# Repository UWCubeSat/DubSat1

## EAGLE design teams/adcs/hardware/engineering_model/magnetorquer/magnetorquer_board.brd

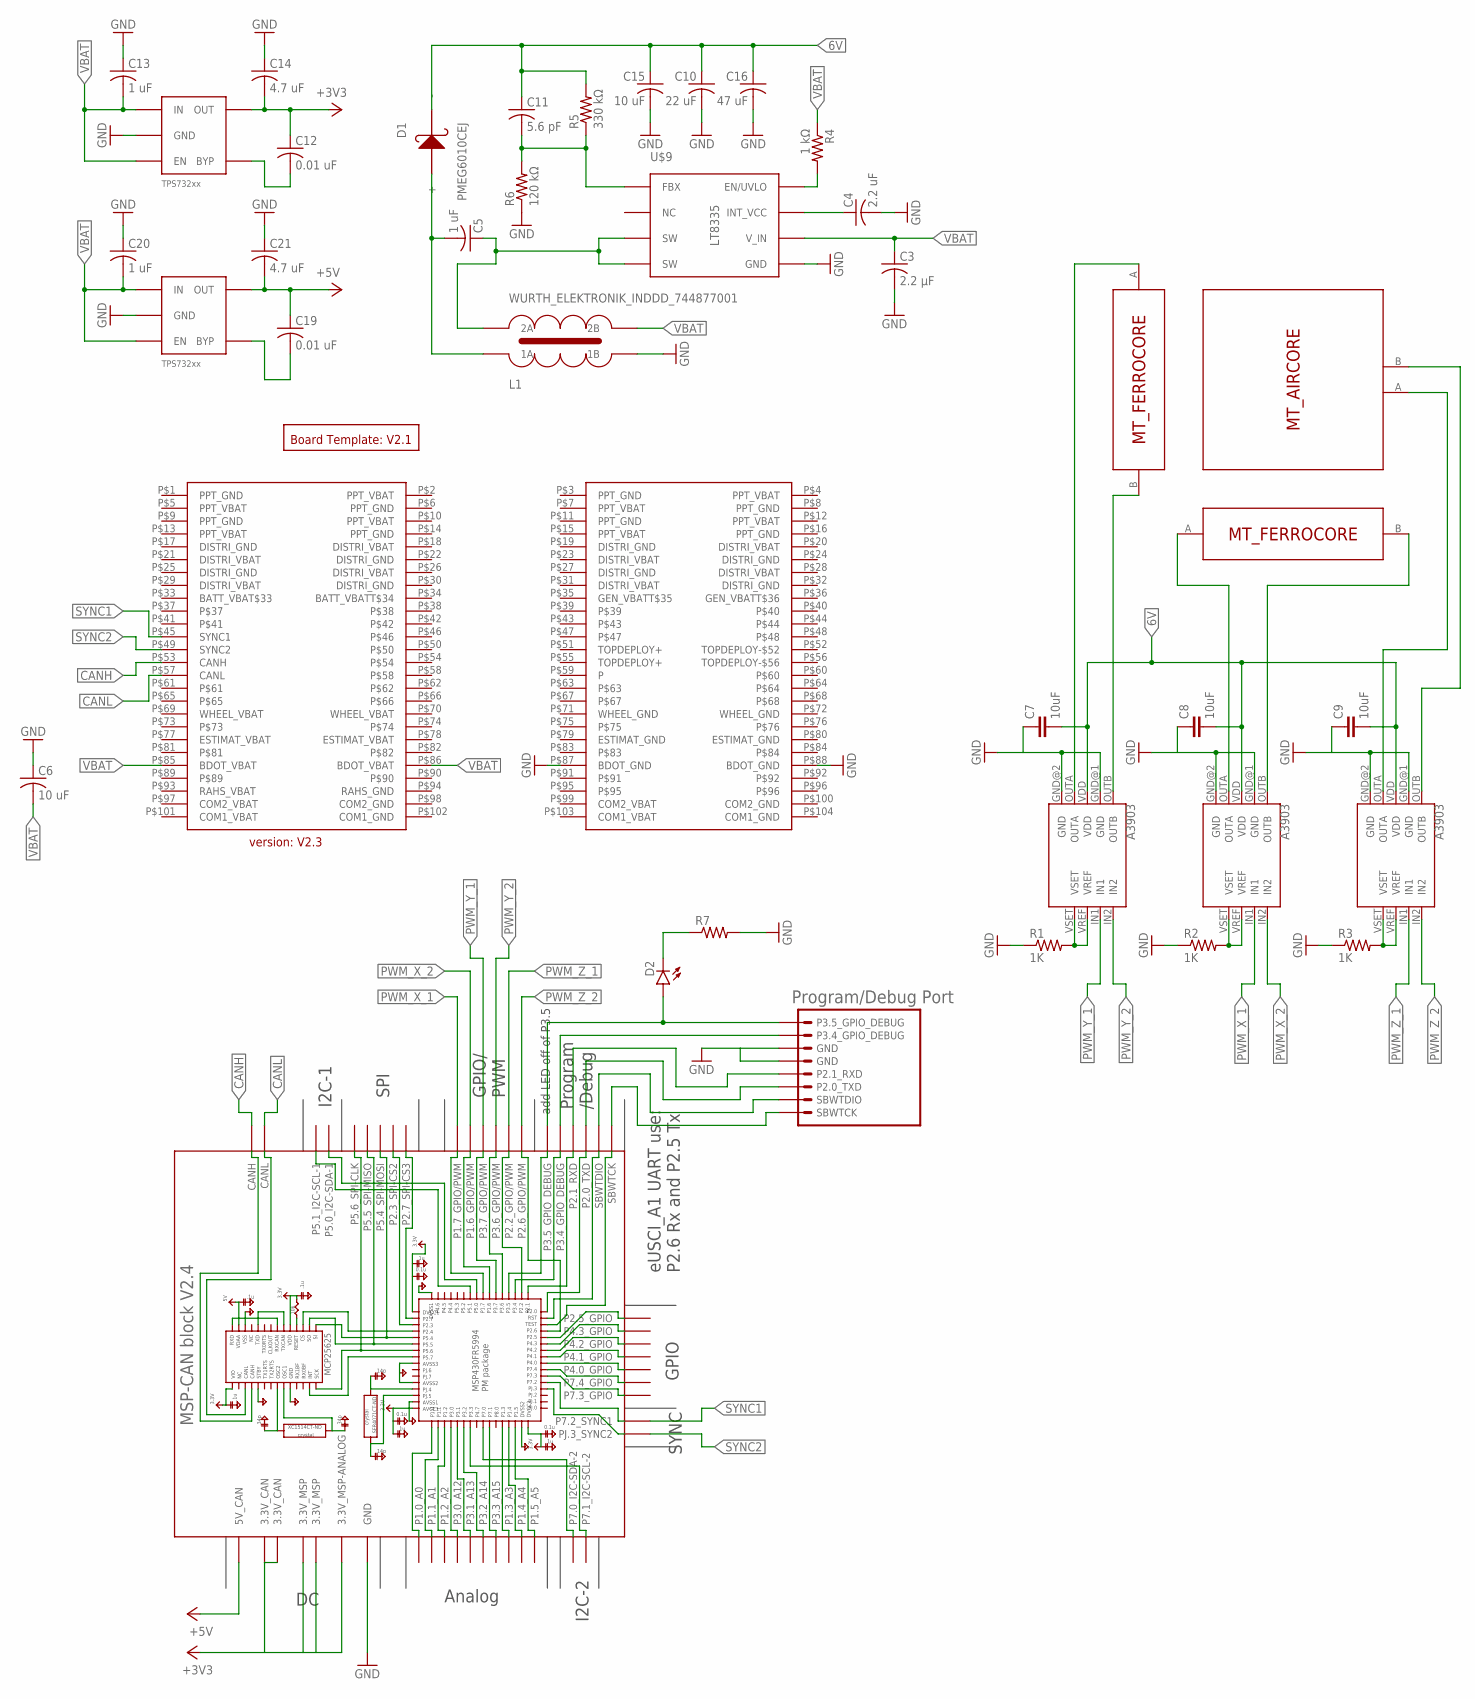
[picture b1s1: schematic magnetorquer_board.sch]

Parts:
C3: 2.2 μF; C0805
C4: 2.2 uF; C0805
C5, C13, C20: 1 uF; C0805
C6, C15: 10 uF; C0805
C7, C8, C9: 10uF; C0805
C10: 22 uF; C1206
C11: 5.6 pF; C0805
C12, C19: 0.01 uF; C0805
C14, C21: 4.7 uF; C0805
C16: 47 uF; C1206
D1: PMEG6010CEJ; SC-90
D2: LED; LED-1206
L1: WURTH_ELEKTRONIK_INDDD_744877001
LDO_3V1, LDO_5V1: TPS732XX; SOT-23-5
R1, R2, R3: 1K; R0603
R4: 1 kΩ; 0805
R5: 330 kΩ; 0805
R6: 120 kΩ; 0805
R7: RESISTOR0805; 0805
U1, U2, U3: A3903; DFN-8EE
U$1: PC104_CONNECTOR
U$2: BOARD_TEMPLATE1; BOARD_TEMPLATE
U$3: MT_AIRCORE
U$4, U$5: MT_FERROCORE
U$7: MSP-CAN_BLOCK
U$8: PROGRAM/DEBUG_PORT; 1X08_CONNECTOR
U$9: LT8335; DDB

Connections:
6V: C7.2, C8.2, C9.2, C10.1, C11.1, C15.1, C16.1, D1.P$2 (-), R5.2, U1.VDD, U2.VDD, U3.VDD
+3V3: C12.1, C14.2, LDO_3V1.P$5 (OUT), U$7.3.3V@CAN1 (3.3V_CAN), U$7.3.3V@CAN2 (3.3V_CAN), U$7.3.3V@MSP1 (3.3V_MSP), U$7.3.3V@MSP2 (3.3V_MSP), U$7.3.3V_ANALOG@MSP2 (3.3V_MSP-ANALOG)
+5V: C19.1, C21.2, LDO_5V1.P$5 (OUT), U$7.5V (5V_CAN)
CANH: U$1.P$53 (CANH), U$7.CANH
CANL: U$1.P$57 (CANL), U$7.CANL
EN_UVLO1: R4.2, U$9.P$8 (EN/UVLO)
FBX: C11.2, R5.1, R6.2, U$9.P$1 (FBX)
GND: C3.2, C4.2, C6.1, C7.1, C8.1, C9.1, C10.2, C13.1, C14.1, C15.2, C16.2, C20.1, C21.1, L1.P$2 (1B), LDO_3V1.P$2 (GND), LDO_5V1.P$2 (GND), R1.1, R2.1, R3.1, R6.1, R7.2, U1.GND@1 (GND), U1.GND@2 (GND), U2.GND@1 (GND), U2.GND@2 (GND), U3.GND@1 (GND), U3.GND@2 (GND), U$1.P$87 (BDOT_GND), U$1.P$88 (BDOT_GND), U$7.GND@1 (GND), U$7.GND@2 (GND), U$7.GND@3 (GND), U$7.GND@4 (GND), U$7.GND@5 (GND), U$7.GND@7 (GND), U$7.GND@8 (GND), U$7.GND@9 (GND), U$7.GND@10 (GND), U$7.GND@11 (GND), U$7.GND@12 (GND), U$7.GND@13 (GND), U$7.GND@14 (GND), U$7.GND@15 (GND), U$7.GND@16 (GND), U$7.GND@17 (GND), U$7.GND@26 (GND), U$8.5 (GND), U$8.6 (GND), U$9.GND, U$9.P$5 (GND)
INT_VCC: C4.1, U$9.P$7 (INT_VCC)
unnamed: R1.2, U1.VREF, U1.VSET
unnamed: R2.2, U2.VREF, U2.VSET
unnamed: D2.C, R7.1
unnamed: C12.2, LDO_3V1.P$4 (BYP)
unnamed: R3.2, U3.VREF, U3.VSET
unnamed: C19.2, LDO_5V1.P$4 (BYP)
unnamed: U1.OUTB, U$4.B
unnamed: U1.OUTA, U$4.A
unnamed: U2.OUTA, U$5.A
unnamed: U2.OUTB, U$5.B
unnamed: U3.OUTB, U$3.B
unnamed: U3.OUTA, U$3.A
unnamed: U$7.SBWTCK, U$8.SBWTCK
unnamed: U$7.SBWTDIO, U$8.2 (SBWTDIO)
unnamed: U$7.P2.0_TXD, U$8.3 (P2.0_TXD)
unnamed: U$7.P2.1_RXD, U$8.4 (P2.1_RXD)
unnamed: U$7.P3.4_GPIO_DEBUG, U$8.7 (P3.4_GPIO_DEBUG)
unnamed: D2.A, U$7.P3.5_GPIO_DEBUG, U$8.8 (P3.5_GPIO_DEBUG)
PWM_X_1: U2.IN1, U$7.P1.7_GPIO/PWM
PWM_X_2: U2.IN2, U$7.P1.6_GPIO/PWM
PWM_Y_1: U1.IN1, U$7.P3.7_GPIO/PWM
PWM_Y_2: U1.IN2, U$7.P3.6_GPIO/PWM
PWM_Z_1: U3.IN1, U$7.P2.2_GPIO/PWM
PWM_Z_2: U3.IN2, U$7.P2.6_GPIO/PWM
SW: C5.1, L1.P$3 (2A), U$9.P$3 (SW), U$9.P$4 (SW)
SYNC1: U$1.P$45 (SYNC1), U$7.P7.2_SYNC1
SYNC2: U$1.P$49 (SYNC2), U$7.PJ.3_SYNC2
VBAT: C3.1, C6.2, C13.2, C20.2, L1.P$4 (2B), LDO_3V1.P$1 (IN), LDO_3V1.P$3 (EN), LDO_5V1.P$1 (IN), LDO_5V1.P$3 (EN), R4.1, U$1.P$85 (BDOT_VBAT), U$1.P$86 (BDOT_VBAT), U$9.P$6 (V_IN)
VD: C5.2, D1.P$1 (+), L1.P$1 (1A)

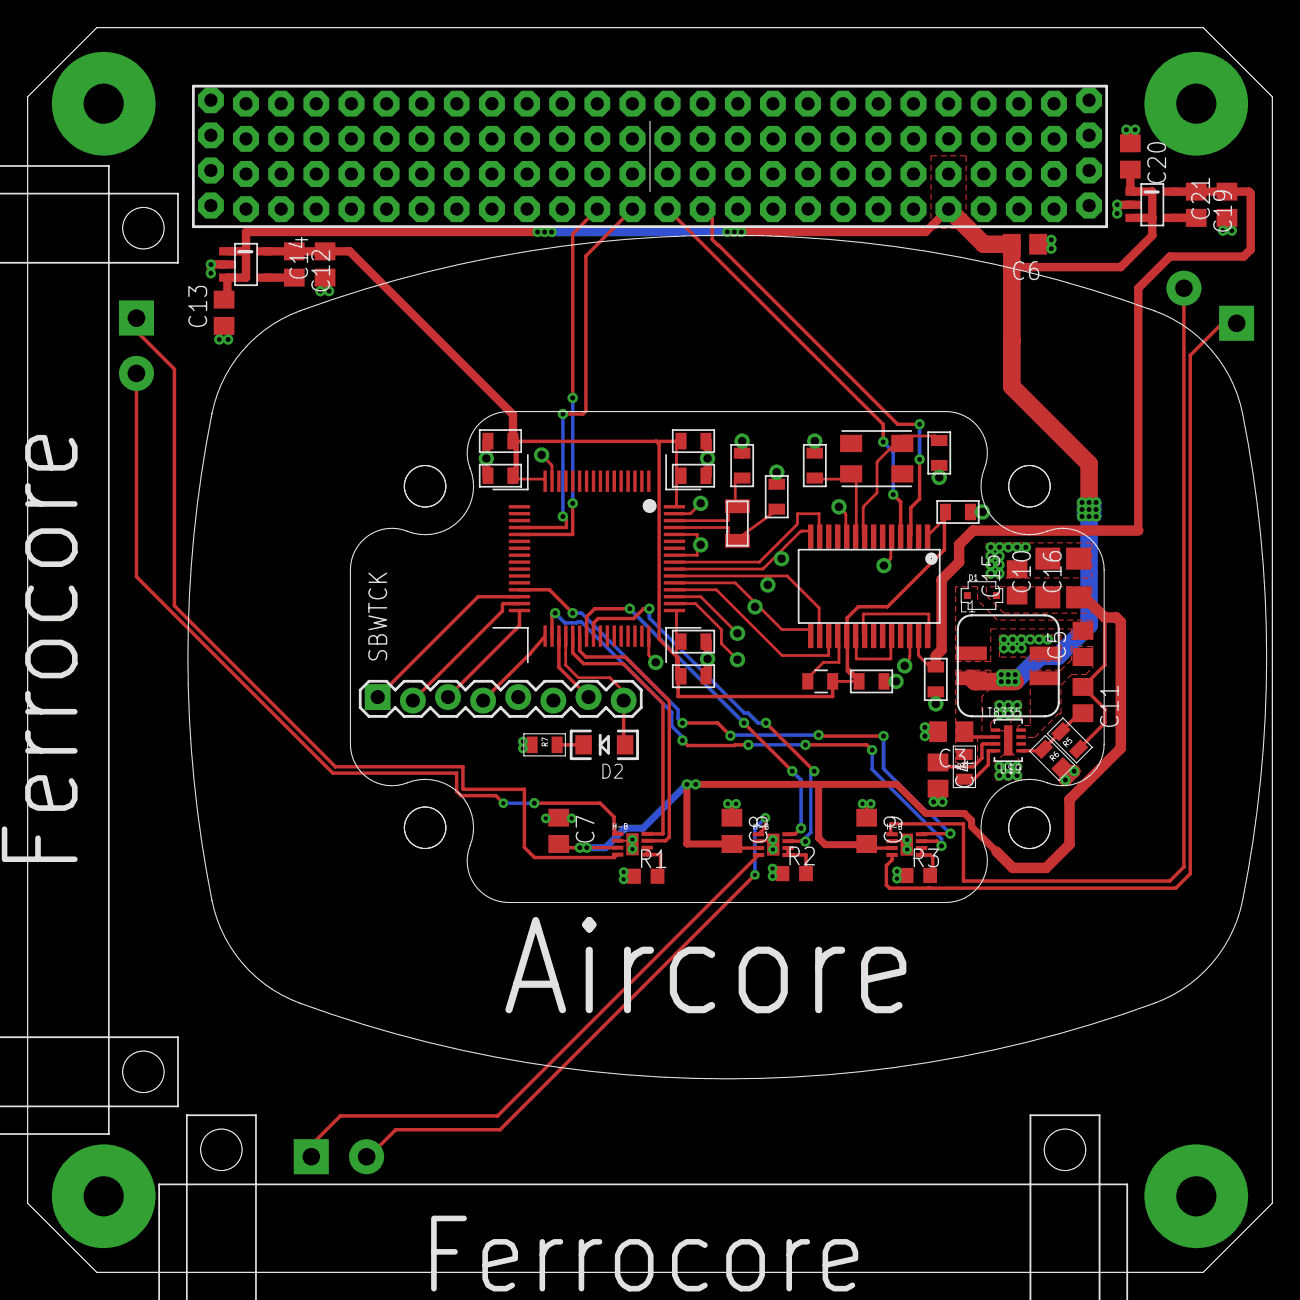
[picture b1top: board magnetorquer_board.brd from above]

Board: 2 copper layers, 90.0 x 90.0 mm, 40 parts (0 on the bottom side), 38 nets.

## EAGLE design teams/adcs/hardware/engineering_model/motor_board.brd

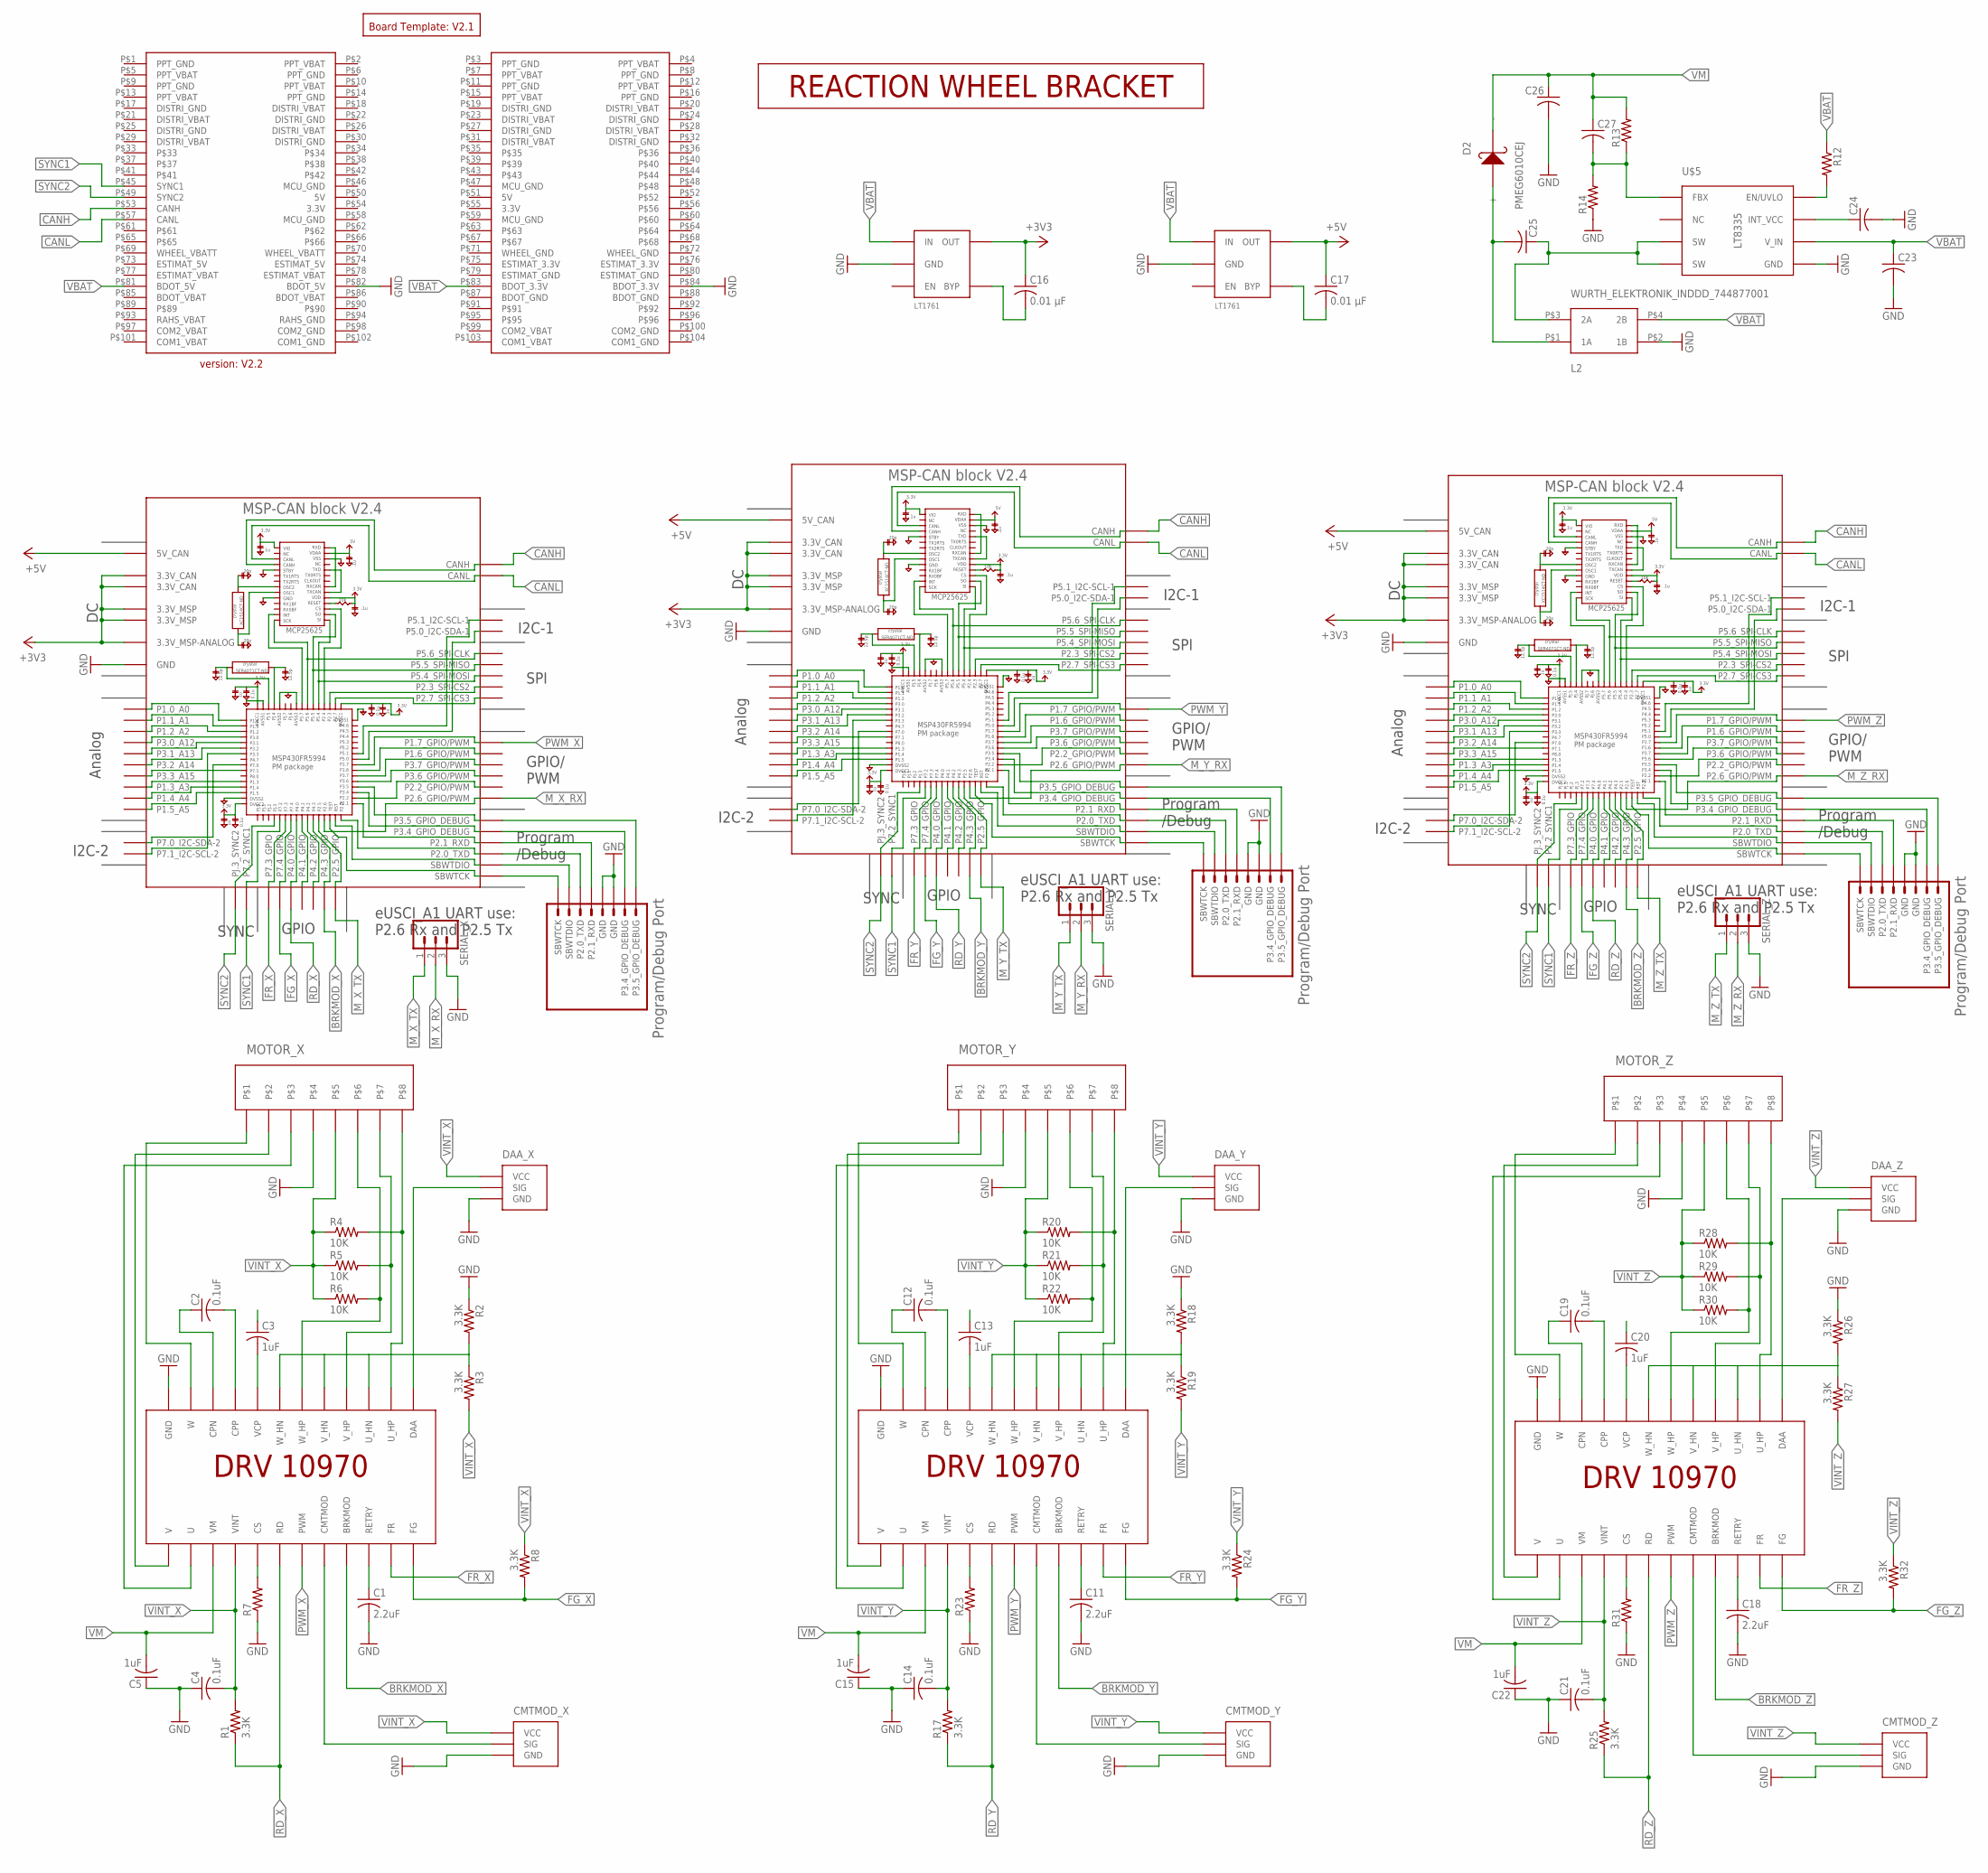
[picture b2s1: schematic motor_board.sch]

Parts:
C1, C11, C18: 2.2uF; C1206
C2, C4, C12, C14, C19, C21: 0.1uF; C0805
C3, C5, C13, C15, C20, C22: 1uF; C1206
C16, C17: 0.01 μF; C0805
C23, C24, C25, C26, C27: C-USC0805; C0805
CMTMOD_X: 0_OHM_JUMPER
CMTMOD_Y: 0_OHM_JUMPER
CMTMOD_Z: 0_OHM_JUMPER
D2: PMEG6010CEJ; SC-90
DAA_X: 0_OHM_JUMPER
DAA_Y: 0_OHM_JUMPER
DAA_Z: 0_OHM_JUMPER
L2: WURTH_ELEKTRONIK_INDDD_744877001
LDO_3V3, LDO_5V: LINEAR_LDO_LT1761-X; SOT-23-5
MOTOR_X: PICOLOCK_8
MOTOR_Y: PICOLOCK_8
MOTOR_Z: PICOLOCK_8
R1, R2, R3, R8, R17, R18, R19, R24, R25, R26, R27, R32: 3.3K; R0805
R4, R5, R6, R20, R21, R22, R28, R29, R30: 10K; R0805
R7, R12, R13, R14, R23, R31: R-US_R0805; R0805
SERIAL_X: CONN_03LOCK; 1X03_LOCK
SERIAL_Y: CONN_03LOCK; 1X03_LOCK
SERIAL_Z: CONN_03LOCK; 1X03_LOCK
U$1: BOARD_TEMPLATE
U$2: PC104_CONNECTOR
U$3, U$10, U$13: MSP-CAN_BLOCK
U$4, U$11, U$14: PROGRAM/DEBUG_PORT; 1X08_CONNECTOR
U$5: LT8335; DDB
U$7, U$12, U$15: DRV10970
U$9: REACTION_WHEEL_BRACKET

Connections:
+3V3: C16.1, LDO_3V3.P$5 (OUT), U$3.3.3V@CAN1 (3.3V_CAN), U$3.3.3V@CAN2 (3.3V_CAN), U$3.3.3V@MSP1 (3.3V_MSP), U$3.3.3V@MSP2 (3.3V_MSP), U$3.3.3V_ANALOG@MSP2 (3.3V_MSP-ANALOG), U$10.3.3V@CAN1 (3.3V_CAN), U$10.3.3V@CAN2 (3.3V_CAN), U$10.3.3V@MSP1 (3.3V_MSP), U$10.3.3V@MSP2 (3.3V_MSP), U$10.3.3V_ANALOG@MSP2 (3.3V_MSP-ANALOG), U$13.3.3V@CAN1 (3.3V_CAN), U$13.3.3V@CAN2 (3.3V_CAN), U$13.3.3V@MSP1 (3.3V_MSP), U$13.3.3V@MSP2 (3.3V_MSP), U$13.3.3V_ANALOG@MSP2 (3.3V_MSP-ANALOG)
+5V: C17.1, LDO_5V.P$5 (OUT), U$3.5V (5V_CAN), U$10.5V (5V_CAN), U$13.5V (5V_CAN)
BRKMOD_X: U$3.P4.3_GPIO, U$7.BRKMOD
BRKMOD_Y: U$10.P4.3_GPIO, U$12.BRKMOD
BRKMOD_Z: U$13.P4.3_GPIO, U$15.BRKMOD
CANH: U$2.P$53 (CANH), U$3.CANH, U$10.CANH, U$13.CANH
CANL: U$2.P$57 (CANL), U$3.CANL, U$10.CANL, U$13.CANL
CMTMOD_X: CMTMOD_X.P$2 (SIG), U$7.CMTMOD
CMTMOD_Y: CMTMOD_Y.P$2 (SIG), U$12.CMTMOD
CMTMOD_Z: CMTMOD_Z.P$2 (SIG), U$15.CMTMOD
CPN_X: C2.1, U$7.CPN
CPN_Y: C12.1, U$12.CPN
CPN_Z: C19.1, U$15.CPN
CPP_X: C2.2, U$7.CPP
CPP_Y: C12.2, U$12.CPP
CPP_Z: C19.2, U$15.CPP
CS_X: R7.2, U$7.CS
CS_Y: R23.2, U$12.CS
CS_Z: R31.2, U$15.CS
DAA_X: DAA_X.P$2 (SIG), U$7.DAA
DAA_Y: DAA_Y.P$2 (SIG), U$12.DAA
DAA_Z: DAA_Z.P$2 (SIG), U$15.DAA
EN_UVLO: R12.2, U$5.P$8 (EN/UVLO)
FBX: C27.2, R13.1, R14.2, U$5.P$1 (FBX)
FG_X: R8.2, U$3.P7.4_GPIO, U$7.FG
FG_Y: R24.2, U$10.P7.4_GPIO, U$12.FG
FG_Z: R32.2, U$13.P7.4_GPIO, U$15.FG
FR_X: U$3.P7.3_GPIO, U$7.FR
FR_Y: U$10.P7.3_GPIO, U$12.FR
FR_Z: U$13.P7.3_GPIO, U$15.FR
GND: C1.2, C3.1, C4.1, C5.1, C11.2, C13.1, C14.1, C15.1, C18.2, C20.1, C21.1, C22.1, C23.2, C24.2, C26.2, CMTMOD_X.P$1 (GND), CMTMOD_Y.P$1 (GND), CMTMOD_Z.P$1 (GND), DAA_X.P$1 (GND), DAA_Y.P$1 (GND), DAA_Z.P$1 (GND), L2.P$2 (1B), LDO_3V3.P$2 (GND), LDO_5V.P$2 (GND), MOTOR_X.P$4, MOTOR_Y.P$4, MOTOR_Z.P$4, R2.1, R7.1, R14.1, R18.1, R23.1, R26.1, R31.1, SERIAL_X.3, SERIAL_Y.3, SERIAL_Z.3, U$2.P$82 (BDOT_5V), U$2.P$84 (BDOT_3.3V), U$3.GND@1 (GND), U$3.GND@2 (GND), U$3.GND@3 (GND), U$3.GND@4 (GND), U$3.GND@5 (GND), U$3.GND@7 (GND), U$3.GND@8 (GND), U$3.GND@9 (GND), U$3.GND@10 (GND), U$3.GND@11 (GND), U$3.GND@12 (GND), U$3.GND@13 (GND), U$3.GND@14 (GND), U$3.GND@15 (GND), U$3.GND@16 (GND), U$3.GND@17 (GND), U$3.GND@26 (GND), U$4.5 (GND), U$4.6 (GND), U$5.GND, U$5.P$5 (GND), U$7.GND@1 (GND), U$7.GND@2 (GND), U$10.GND@1 (GND), U$10.GND@2 (GND), U$10.GND@3 (GND), U$10.GND@4 (GND), U$10.GND@5 (GND), U$10.GND@7 (GND), U$10.GND@8 (GND), U$10.GND@9 (GND), U$10.GND@10 (GND), U$10.GND@11 (GND), U$10.GND@12 (GND), U$10.GND@13 (GND), U$10.GND@14 (GND), U$10.GND@15 (GND), U$10.GND@16 (GND), U$10.GND@17 (GND), U$10.GND@26 (GND), U$11.5 (GND), U$11.6 (GND), U$12.GND@1 (GND), U$12.GND@2 (GND), U$13.GND@1 (GND), U$13.GND@2 (GND), U$13.GND@3 (GND), U$13.GND@4 (GND), U$13.GND@5 (GND), U$13.GND@7 (GND), U$13.GND@8 (GND), U$13.GND@9 (GND), U$13.GND@10 (GND), U$13.GND@11 (GND), U$13.GND@12 (GND), U$13.GND@13 (GND), U$13.GND@14 (GND), U$13.GND@15 (GND), U$13.GND@16 (GND), U$13.GND@17 (GND), U$13.GND@26 (GND), U$14.5 (GND), U$14.6 (GND), U$15.GND@1 (GND), U$15.GND@2 (GND)
GPIO_DEBUG_3.4_X: U$3.P3.4_GPIO_DEBUG, U$4.7 (P3.4_GPIO_DEBUG)
GPIO_DEBUG_3.4_Y: U$10.P3.4_GPIO_DEBUG, U$11.7 (P3.4_GPIO_DEBUG)
GPIO_DEBUG_3.4_Z: U$13.P3.4_GPIO_DEBUG, U$14.7 (P3.4_GPIO_DEBUG)
GPIO_DEBUG_3.5_X: U$3.P3.5_GPIO_DEBUG, U$4.8 (P3.5_GPIO_DEBUG)
GPIO_DEBUG_3.5_Y: U$10.P3.5_GPIO_DEBUG, U$11.8 (P3.5_GPIO_DEBUG)
GPIO_DEBUG_3.5_Z: U$13.P3.5_GPIO_DEBUG, U$14.8 (P3.5_GPIO_DEBUG)
HN_X: R2.2, R3.1, U$7.U_HN, U$7.V_HN, U$7.W_HN
HN_Y: R18.2, R19.1, U$12.U_HN, U$12.V_HN, U$12.W_HN
HN_Z: R26.2, R27.1, U$15.U_HN, U$15.V_HN, U$15.W_HN
HP_U_X: MOTOR_X.P$8, R4.2, U$7.U_HP
HP_U_Y: MOTOR_Y.P$8, R20.2, U$12.U_HP
HP_U_Z: MOTOR_Z.P$8, R28.2, U$15.U_HP
HP_V_X: MOTOR_X.P$7, R5.2, U$7.V_HP
HP_V_Y: MOTOR_Y.P$7, R21.2, U$12.V_HP
HP_V_Z: MOTOR_Z.P$7, R29.2, U$15.V_HP
HP_W_X: MOTOR_X.P$6, R6.2, U$7.W_HP
HP_W_Y: MOTOR_Y.P$6, R22.2, U$12.W_HP
HP_W_Z: MOTOR_Z.P$6, R30.2, U$15.W_HP
INT_VCC: C24.1, U$5.P$7 (INT_VCC)
M_X_RX: SERIAL_X.2, U$3.P2.6_GPIO/PWM
M_X_TX: SERIAL_X.1, U$3.P2.5_GPIO
M_Y_RX: SERIAL_Y.2, U$10.P2.6_GPIO/PWM
M_Y_TX: SERIAL_Y.1, U$10.P2.5_GPIO
M_Z_RX: SERIAL_Z.2, U$13.P2.6_GPIO/PWM
M_Z_TX: SERIAL_Z.1, U$13.P2.5_GPIO
unnamed: C25.2, D2.P$1 (+), L2.P$1 (1A)
unnamed: C17.2, LDO_5V.P$4 (BYP)
unnamed: C16.2, LDO_3V3.P$4 (BYP)
PWM_X: U$3.P1.7_GPIO/PWM, U$7.PWM
PWM_Y: U$10.P1.7_GPIO/PWM, U$12.PWM
PWM_Z: U$13.P1.7_GPIO/PWM, U$15.PWM
RD_X: R1.1, U$3.P4.0_GPIO, U$7.RD
RD_Y: R17.1, U$10.P4.0_GPIO, U$12.RD
RD_Z: R25.1, U$13.P4.0_GPIO, U$15.RD
RETRY_X: C1.1, U$7.RETRY
RETRY_Y: C11.1, U$12.RETRY
RETRY_Z: C18.1, U$15.RETRY
RXD_X: U$3.P2.1_RXD, U$4.4 (P2.1_RXD)
RXD_Y: U$10.P2.1_RXD, U$11.4 (P2.1_RXD)
RXD_Z: U$13.P2.1_RXD, U$14.4 (P2.1_RXD)
SBWTCK_X: U$3.SBWTCK, U$4.SBWTCK
SBWTCK_Y: U$10.SBWTCK, U$11.SBWTCK
SBWTCK_Z: U$13.SBWTCK, U$14.SBWTCK
SBWTDIO_X: U$3.SBWTDIO, U$4.2 (SBWTDIO)
SBWTDIO_Y: U$10.SBWTDIO, U$11.2 (SBWTDIO)
SBWTDIO_Z: U$13.SBWTDIO, U$14.2 (SBWTDIO)
SW: C25.1, L2.P$3 (2A), U$5.P$3 (SW), U$5.P$4 (SW)
SYNC1: U$2.P$45 (SYNC1), U$3.P7.2_SYNC1, U$10.P7.2_SYNC1, U$13.P7.2_SYNC1
SYNC2: U$2.P$49 (SYNC2), U$3.PJ.3_SYNC2, U$10.PJ.3_SYNC2, U$13.PJ.3_SYNC2
TXD_X: U$3.P2.0_TXD, U$4.3 (P2.0_TXD)
TXD_Y: U$10.P2.0_TXD, U$11.3 (P2.0_TXD)
TXD_Z: U$13.P2.0_TXD, U$14.3 (P2.0_TXD)
U_X: MOTOR_X.P$3, U$7.U
U_Y: MOTOR_Y.P$3, U$12.U
U_Z: MOTOR_Z.P$3, U$15.U
VBAT: C23.1, L2.P$4 (2B), LDO_3V3.P$1 (IN), LDO_5V.P$1 (IN), R12.1, U$2.P$81 (BDOT_5V), U$2.P$83 (BDOT_3.3V), U$5.P$6 (V_IN)
VCP_X: C3.2, U$7.VCP
VCP_Y: C13.2, U$12.VCP
VCP_Z: C20.2, U$15.VCP
VINT_X: C4.2, CMTMOD_X.P$3 (VCC), DAA_X.P$3 (VCC), MOTOR_X.P$5, R1.2, R3.2, R4.1, R5.1, R6.1, R8.1, U$7.VINT
VINT_Y: C14.2, CMTMOD_Y.P$3 (VCC), DAA_Y.P$3 (VCC), MOTOR_Y.P$5, R17.2, R19.2, R20.1, R21.1, R22.1, R24.1, U$12.VINT
VINT_Z: C21.2, CMTMOD_Z.P$3 (VCC), DAA_Z.P$3 (VCC), MOTOR_Z.P$5, R25.2, R27.2, R28.1, R29.1, R30.1, R32.1, U$15.VINT
VM: C5.2, C15.2, C22.2, C26.1, C27.1, D2.P$2 (-), R13.2, U$7.VM, U$12.VM, U$15.VM
V_X: MOTOR_X.P$2, U$7.V
V_Y: MOTOR_Y.P$2, U$12.V
V_Z: MOTOR_Z.P$2, U$15.V
W_X: MOTOR_X.P$1, U$7.W
W_Y: MOTOR_Y.P$1, U$12.W
W_Z: MOTOR_Z.P$1, U$15.W

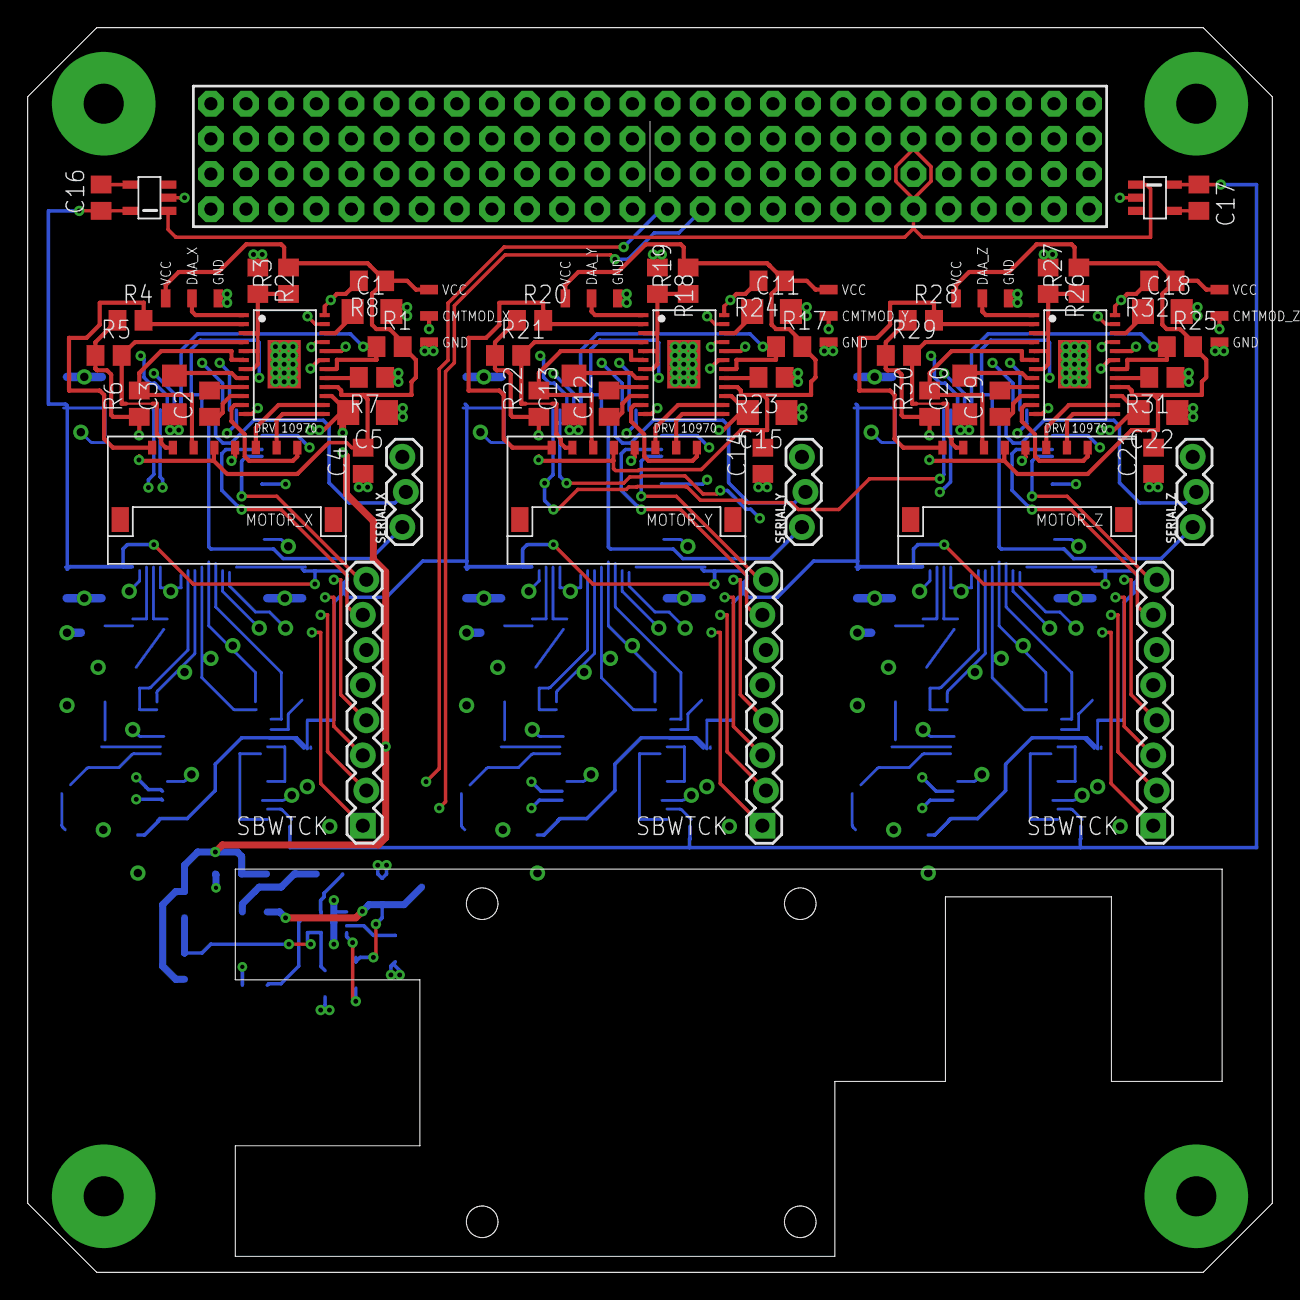
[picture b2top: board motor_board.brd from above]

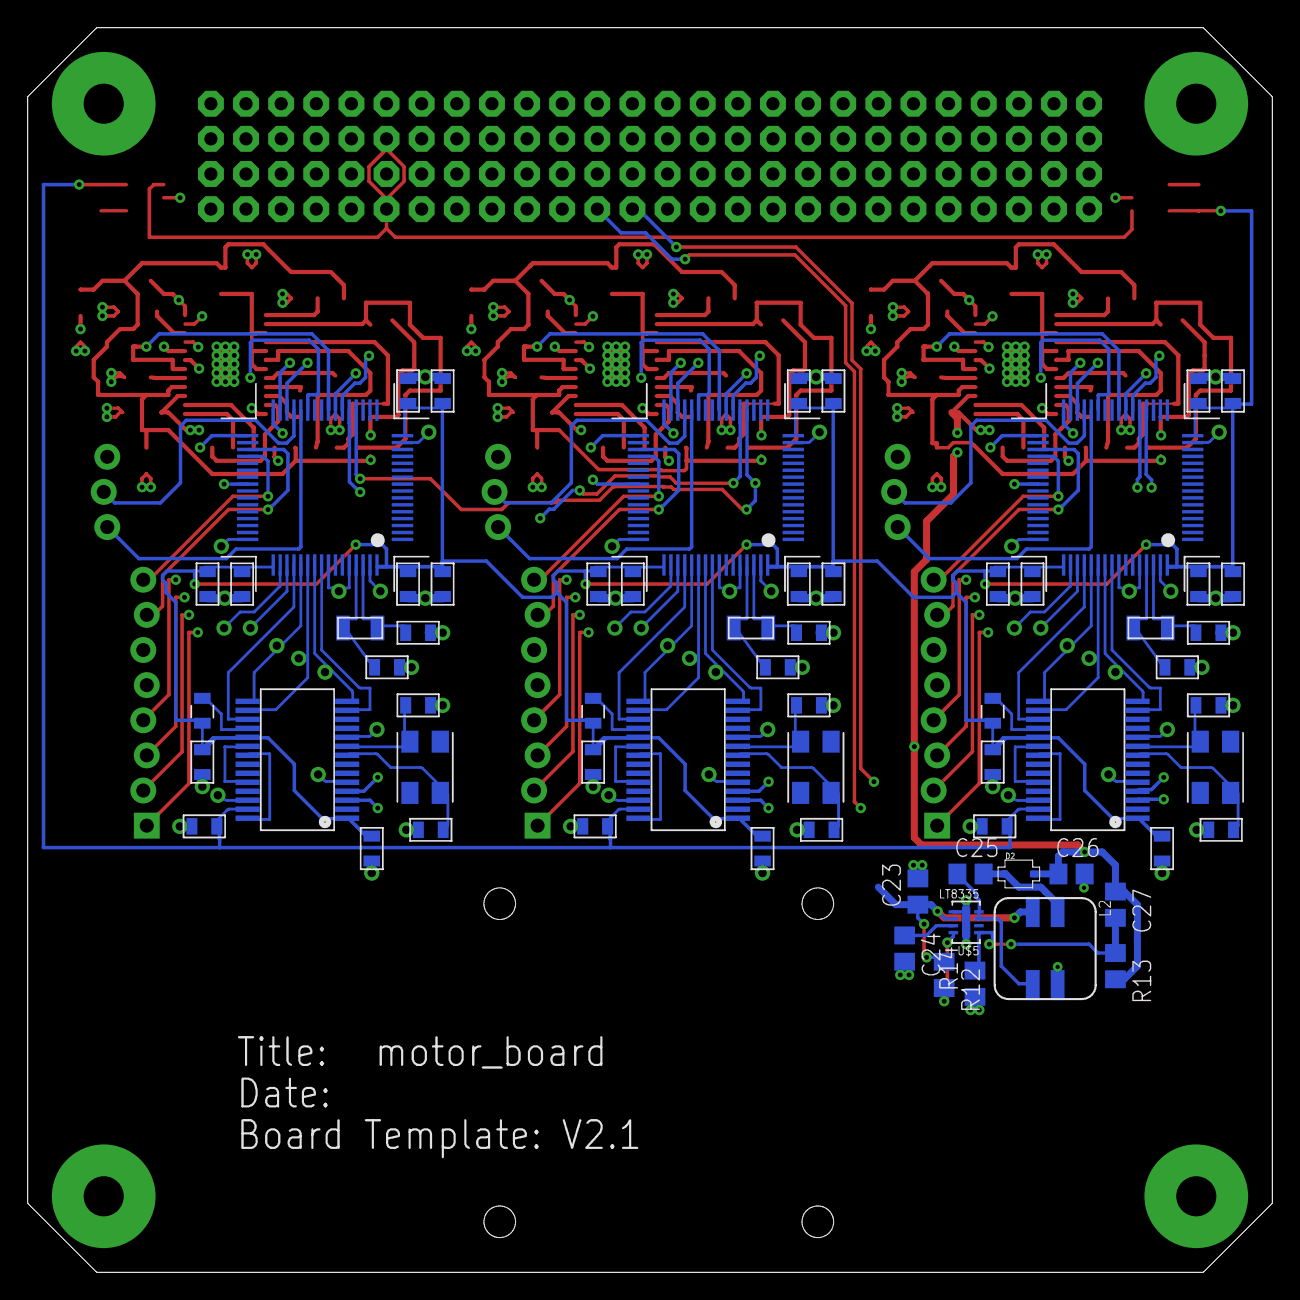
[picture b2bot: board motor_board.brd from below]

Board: 4 copper layers, 90.0 x 90.0 mm, 78 parts (14 on the bottom side), 100 nets.

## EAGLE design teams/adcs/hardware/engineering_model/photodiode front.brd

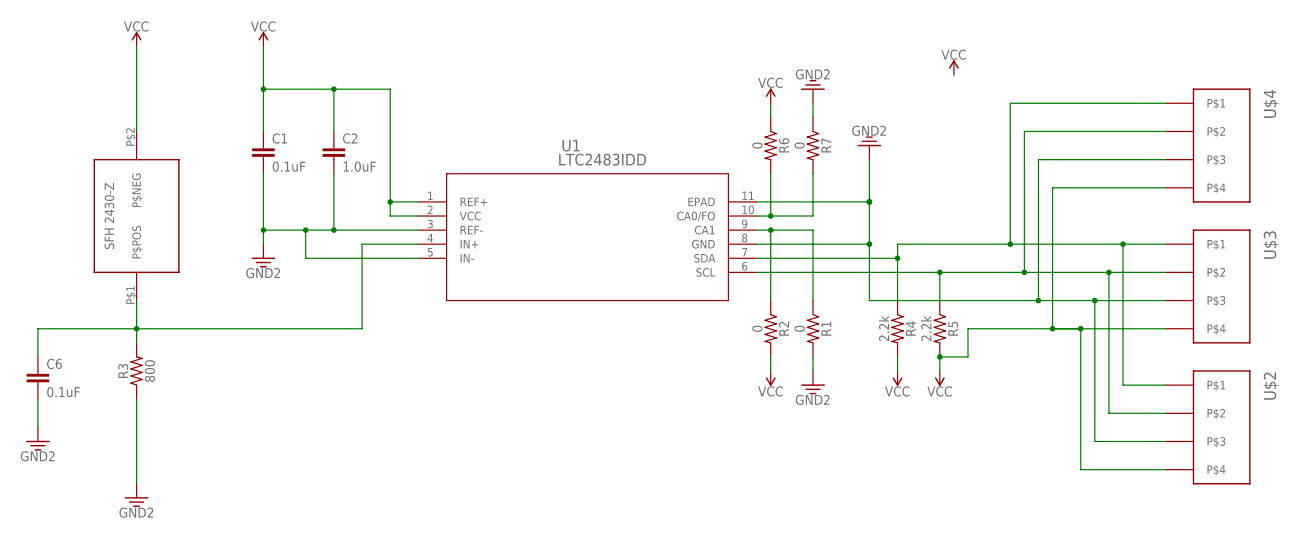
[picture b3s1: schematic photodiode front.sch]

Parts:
C1, C6: 0.1uF; 0805
C2: 1.0uF; 0805
R1, R2, R6, R7: 0; 0805
R3: 800; 0805
R4, R5: 2.2k; 0805
U1: LTC2483IDD; DFN-10_DD
U$1: SFH-2430-Z; DIL
U$2, U$3, U$4: PICOLOCK_4PICOLOCK_4; PICOLOCK_4

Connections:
CA0: R6.2, R7.2, U1.10 (CA0/FO)
CA1: R1.1, R2.1, U1.9 (CA1)
GND: C1.2, C2.2, C6.2, R1.2, R3.1, R7.1, U1.3 (REF-), U1.5 (IN-), U1.8 (GND), U1.11 (EPAD), U$2.P$3, U$3.P$3, U$4.P$3
OUTPUT: C6.1, R3.2, U1.4 (IN+), U$1.P$1 (P$POS)
SCL: R5.1, U1.6 (SCL), U$2.P$2, U$3.P$2, U$4.P$2
SDA: R4.1, U1.7 (SDA), U$2.P$1, U$3.P$1, U$4.P$1
VCC: C1.1, C2.1, R2.2, R4.2, R5.2, R6.1, U1.1 (REF+), U1.2 (VCC), U$1.P$2 (P$NEG), U$2.P$4, U$3.P$4, U$4.P$4

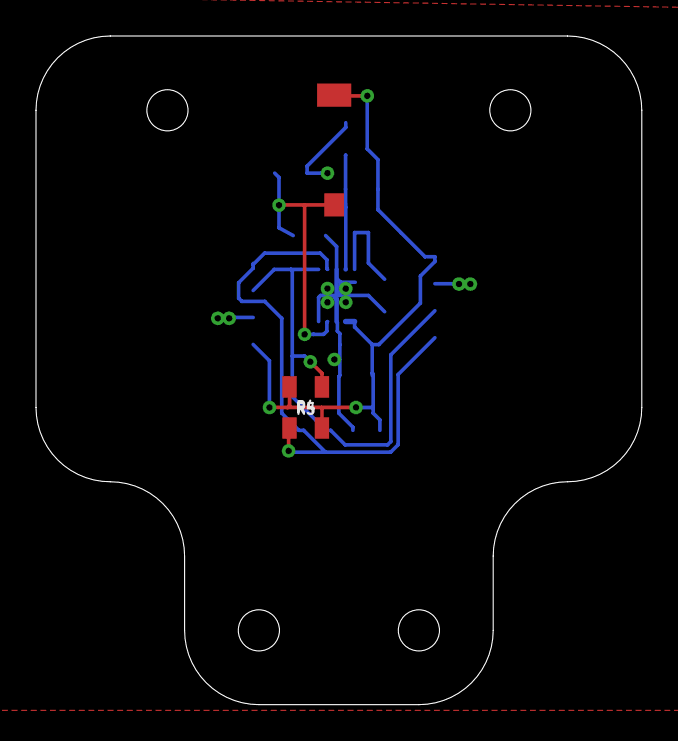
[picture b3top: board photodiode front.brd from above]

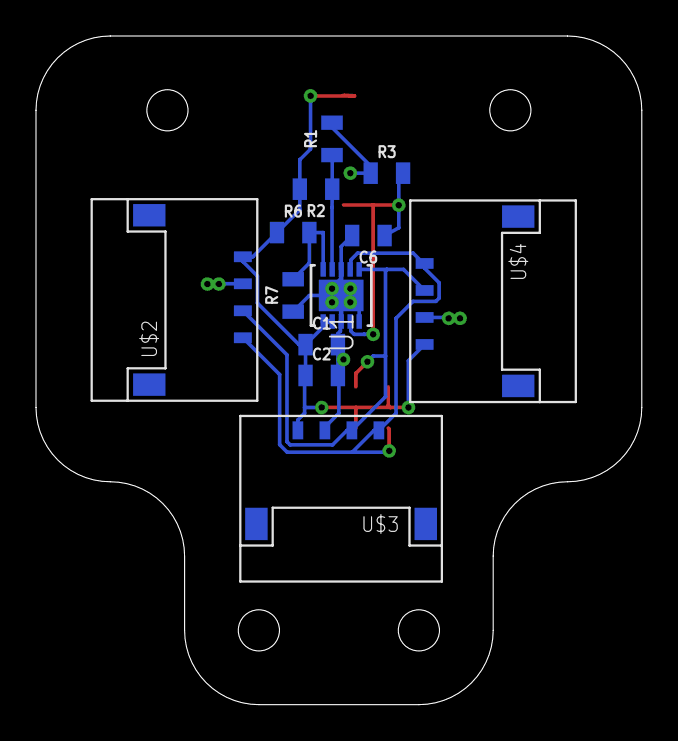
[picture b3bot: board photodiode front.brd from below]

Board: 2 copper layers, 33.7 x 37.1 mm, 15 parts (12 on the bottom side), 7 nets.

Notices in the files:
parts and their libraries:
SparkFun-Connectors: Licensing: Creative Commons ShareAlike 4.0 International - https://creativecommons.org/licenses/by-sa/4.0
